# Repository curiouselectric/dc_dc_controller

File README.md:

# dc_dc_controller
A logic controlled DC-DC step up converter PCB

Have you needed to power a small sensor with 12 or 24V but only had 3.3V or 5V available?
Maybe you need to really reduce your power consumption and running the sensor all the time will consume too much power?
Then this simple logic-controller DC-DC step-up converter might be useful for you!

The step-up converter is an off-the-shelf DC-DC converter board using the MT3608. This can take an input voltage of 2-24V DC and supply an output voltage up to 28V DC. Up to 2A can be supplied (but not recommended for any length of time).

While this converter is useful, what if you only want to check your sensor every 10 mins or hour? Keeping the sensor powered up with a DC-DC converter will just waste energy, which might be in short supply from a battery-based system. So, we added a MOSFET based logic-controlled switch. You apply 3.3V - 5V to the control input and it will switch on the DC-DC converter. Your device can wake up, check your sensor, then go back to sleep and save lots of energy.

We have used this circuit for a weather monitoring station.

This is a reasonably simple kit which requires a small amount of soldering.
It should take under 1 hour to build.
Not suitable for under 12 years old.

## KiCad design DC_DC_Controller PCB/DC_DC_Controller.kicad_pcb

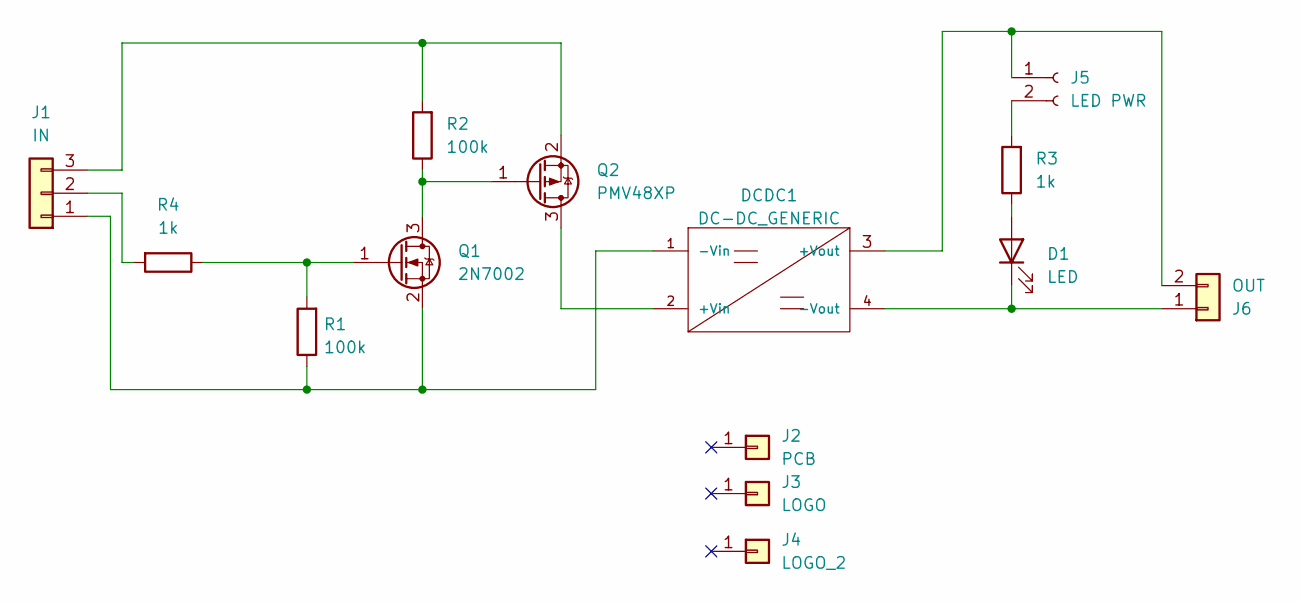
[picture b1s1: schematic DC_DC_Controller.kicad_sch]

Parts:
D1: LED; SM0805_LED; LCSC C84256
DCDC1: DC-DC_GENERIC; TH_DCDC_Step_up_MT3608
J1: IN; SIL-3_screw_terminal
J2: PCB; PCB_DC_DC_Outline_v1
J3: LOGO; 2019_011_16_CuriousElectricCompany_Logo_Round_Logo_No_words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
J4: LOGO_2; TCEC_Words_13mm
J5: LED PWR; SIL-2_solder_connect_2
J6: OUT; SIL-2_screw_terminal
Q1: 2N7002; SOT-23; LCSC C8545
Q2: PMV48XP; SOT-23; LCSC C2959854
R1, R2: 100k; SM0805; JLCPCB Add Y
R3, R4: 1k; SM0805; JLCPCB Add Y

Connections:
unnamed: D1.1 (K), DCDC1.4 (-Vout), J6.1
unnamed: D1.2 (A), R3.1
unnamed: DCDC1.1 (-Vin), J1.1, Q1.2 (S), R1.1
unnamed: DCDC1.2 (+Vin), Q2.3 (D)
unnamed: DCDC1.3 (+Vout), J5.1, J6.2
unnamed: J1.2, R4.2
unnamed: J1.3, Q2.2 (S), R2.2
unnamed: J5.2, R3.2
unnamed: Q1.1 (G), R1.2, R4.1
unnamed: Q1.3 (D), Q2.1 (G), R2.1

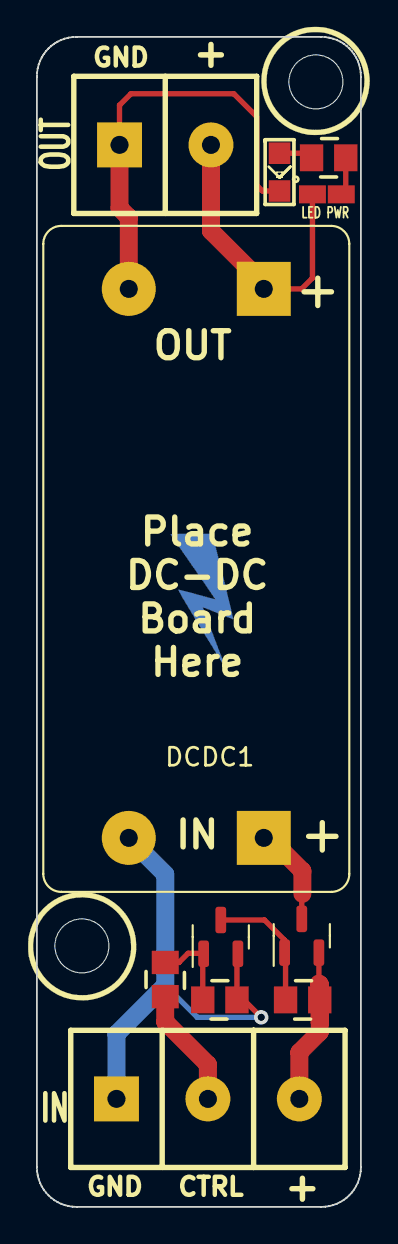
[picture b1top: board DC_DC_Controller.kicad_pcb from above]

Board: 2 copper layers, 18.0 x 65.0 mm, 14 parts (1 on the bottom side), 10 nets.

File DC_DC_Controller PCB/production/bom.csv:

Designator,Footprint,Quantity,Value,LCSC Part #
D1,SM0805_LED,1,LED,C84256
DCDC1,TH_DCDC_Step_up_MT3608,1,DC-DC_GENERIC,
J1,SIL-3_screw_terminal,1,IN,
J2,PCB_DC_DC_Outline_v1,1,PCB,
J3,2019_011_16_CuriousElectricCompany_Logo_Round_Logo_No_words_KiCAD_10mm_PCBLogo,1,LOGO,
J4,TCEC_Words_13mm,1,LOGO_2,
J5,SIL-2_solder_connect_2,1,LED PWR,
J6,SIL-2_screw_terminal,1,OUT,
Q1,SOT-23,1,2N7002,C8545
Q2,SOT-23,1,PMV48XP,C2959854
"R1, R2",SM0805,2,100k,C103905
"R3, R4",SM0805,2,1k,C103903

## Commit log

2023-07-12 images changed
